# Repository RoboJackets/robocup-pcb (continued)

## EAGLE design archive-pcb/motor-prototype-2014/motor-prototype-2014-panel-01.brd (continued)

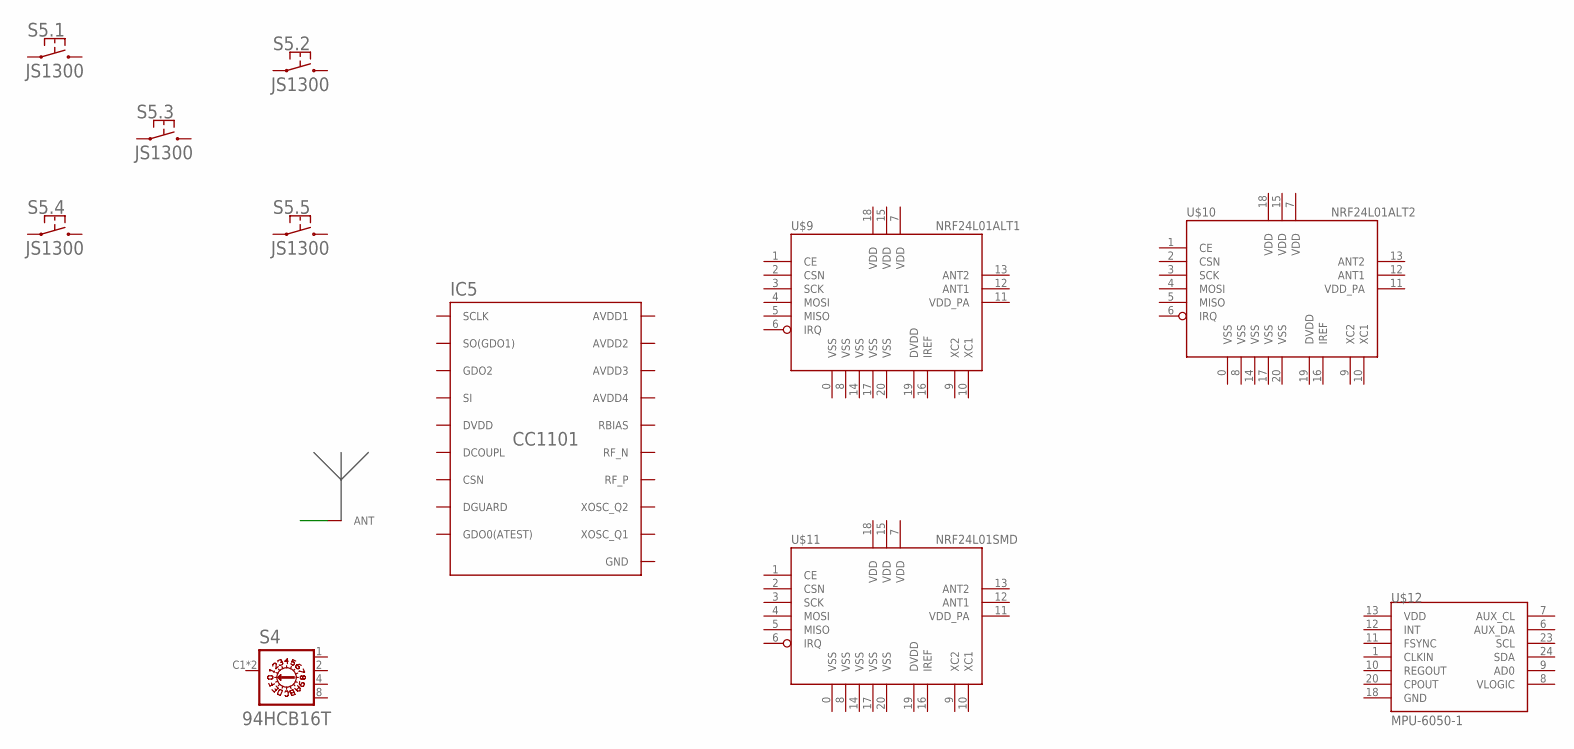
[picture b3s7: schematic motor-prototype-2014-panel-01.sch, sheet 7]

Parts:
916MHZ: ANT-916-CHP-T; ANT-916-CHP
IC5: CC1101; QLP20
S4: 94HCB16T; HEX
S5: JS1300
U$9: NRF24L01ALT1; QFN20_ALT1
U$10: NRF24L01ALT2; QFN20_ALT2
U$11: NRF24L01SMD; QFN20
U$12: MPU-6050-1; QFN-24-4MM2

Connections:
ANT_COPPER: 916MHZ.ANT
DVDD: U$9.19 (DVDD), U$10.19 (DVDD), U$11.19 (DVDD)
VDD: U$9.7 (VDD), U$9.15 (VDD), U$9.18 (VDD), U$10.7 (VDD), U$10.15 (VDD), U$10.18 (VDD), U$11.7 (VDD), U$11.15 (VDD), U$11.18 (VDD); also elsewhere on the board
VDD_PA: U$9.11 (VDD_PA), U$10.11 (VDD_PA), U$11.11 (VDD_PA)
VSS: U$9.0 (VSS), U$9.8 (VSS), U$9.14 (VSS), U$9.17 (VSS), U$9.20 (VSS), U$10.0 (VSS), U$10.8 (VSS), U$10.14 (VSS), U$10.17 (VSS), U$10.20 (VSS), U$11.0 (VSS), U$11.8 (VSS), U$11.14 (VSS), U$11.17 (VSS), U$11.20 (VSS); also elsewhere on the board

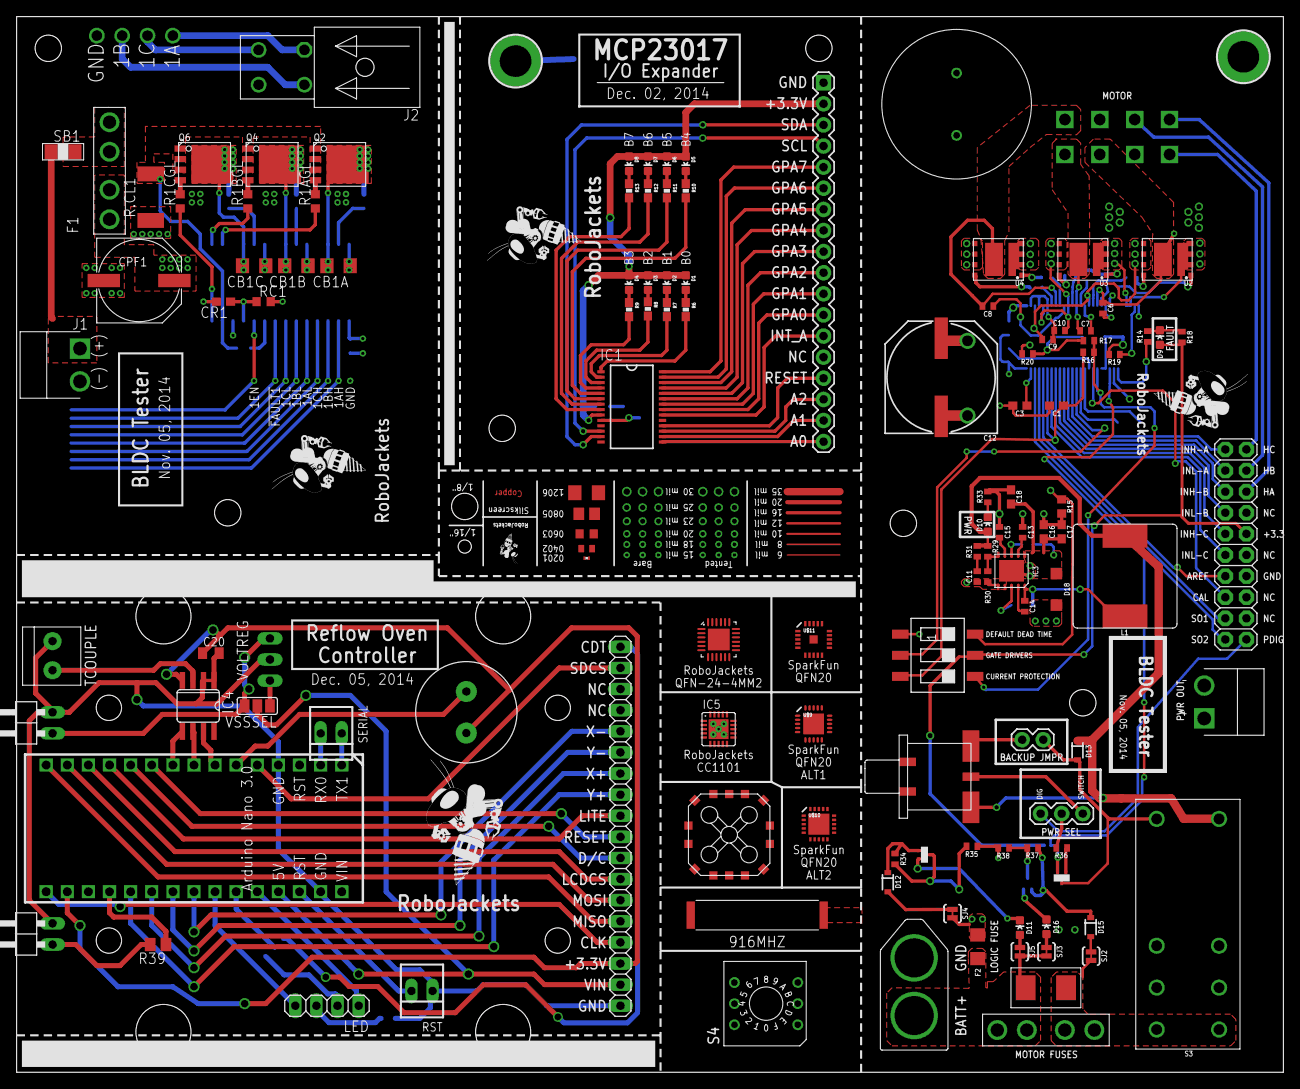
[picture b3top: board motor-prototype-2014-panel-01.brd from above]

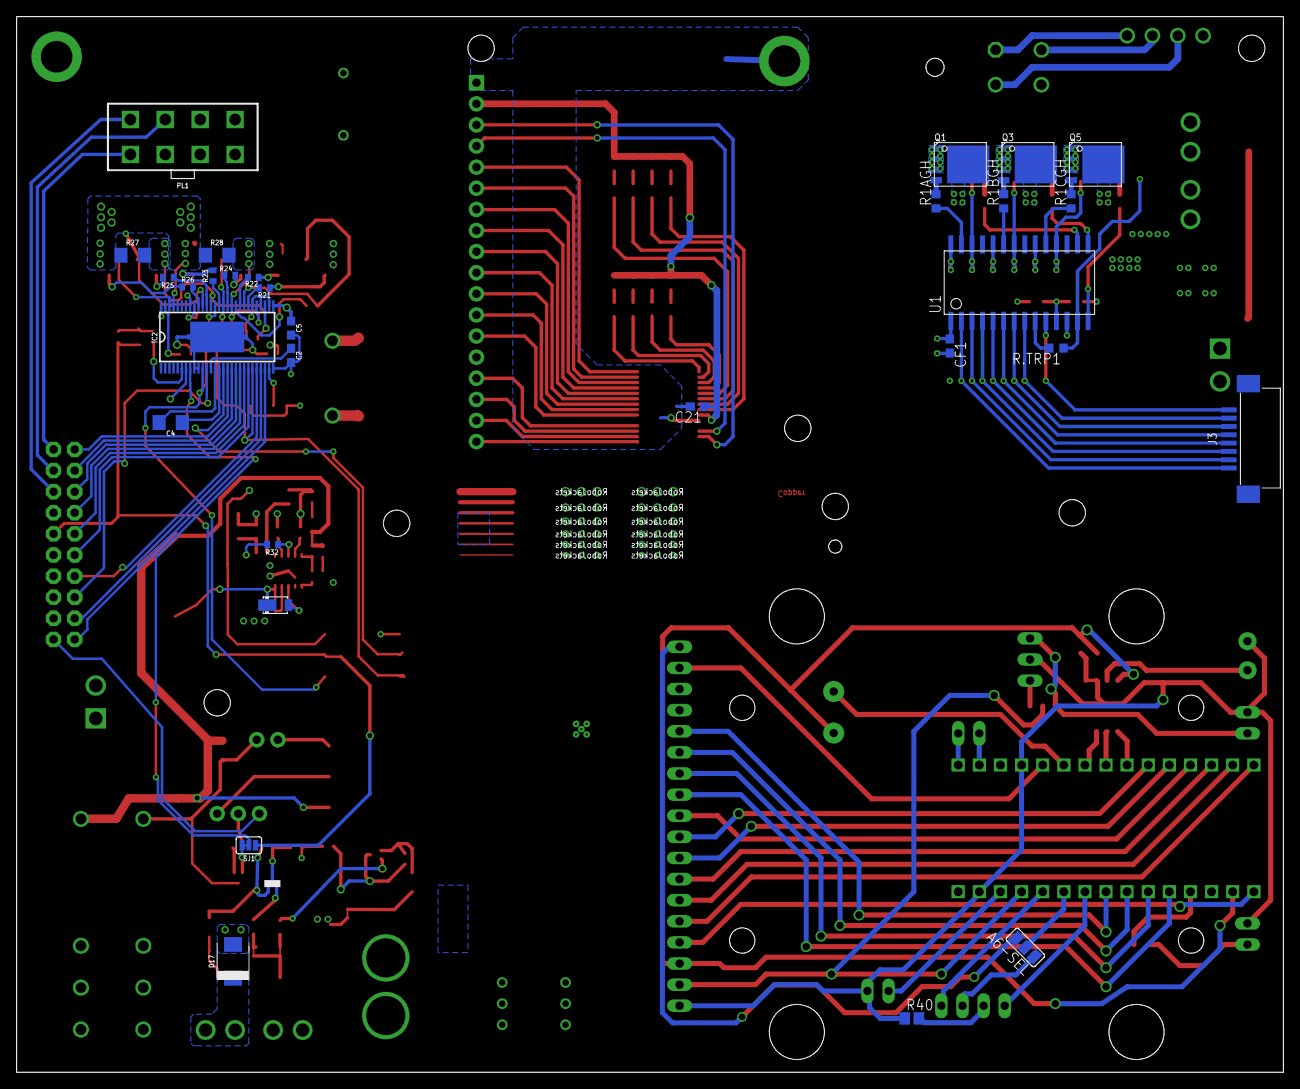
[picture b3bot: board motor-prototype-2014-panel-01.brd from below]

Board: 4 copper layers, 152.4 x 127.0 mm, 162 parts (31 on the bottom side), 172 nets.

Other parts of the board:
U$1, U$5, U$6: ROBOBUZZ_0.6X
U$3: ROBOBUZZ_0.2X
U$8: ROBOBUZZ_0.8X

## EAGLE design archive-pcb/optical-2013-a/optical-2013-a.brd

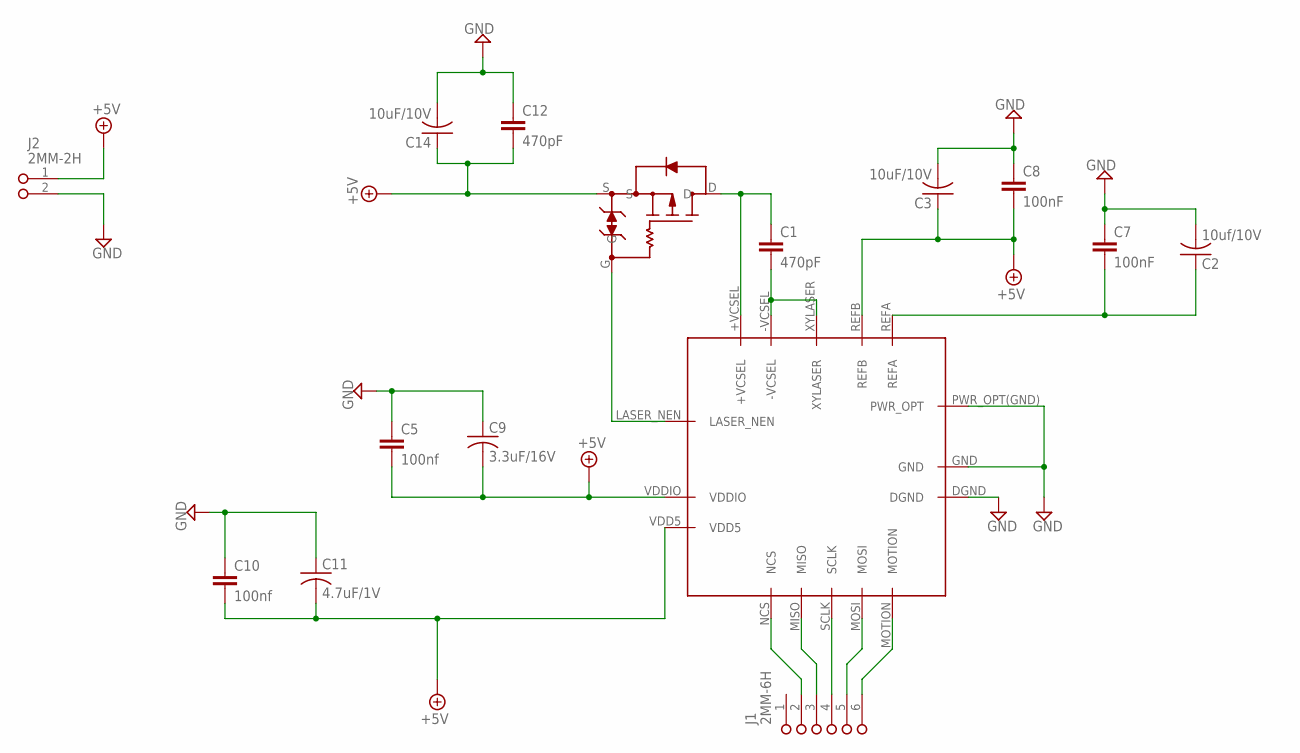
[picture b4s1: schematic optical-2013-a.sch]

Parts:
C1, C12: 470pF; C1005
C2: 10uf/10V; C1005
C3, C14: 10uF/10V; C1005
C5, C10: 100nf; C1005
C7, C8: 100nF; C1005
C9: 3.3uF/16V; C1005
C11: 4.7uF/1V; C1005
J1: 2MM-6H; 2MM-6-H
J2: 2MM-2H; 2MM-2-H
U$1: OPTICAL_SENSOR; ADNS-9500
U$2: P-CHANNEL_MOSFET; NTA4151P

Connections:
+5V: C3.1, C5.2, C8.2, C9.2, C10.2, C11.2, C12.2, C14.1, J2.1, U$1.REFB, U$1.VDD5, U$1.VDDIO, U$2.S
GND: C2.2, C3.2, C5.1, C7.1, C8.1, C9.1, C10.1, C11.1, C12.1, C14.2, J2.2, U$1.DGND, U$1.GND, U$1.PWR_OPT(GND) (PWR_OPT)
unnamed: J1.5, U$1.MOSI
unnamed: J1.6, U$1.MOTION
unnamed: J1.4, U$1.SCLK
unnamed: J1.3, U$1.MISO
unnamed: J1.2, U$1.NCS
unnamed: U$1.LASER_NEN, U$2.G
unnamed: C1.1, U$1.+VCSEL, U$2.D
unnamed: C1.2, U$1.-VCSEL, U$1.XYLASER
unnamed: C2.1, C7.2, U$1.REFA

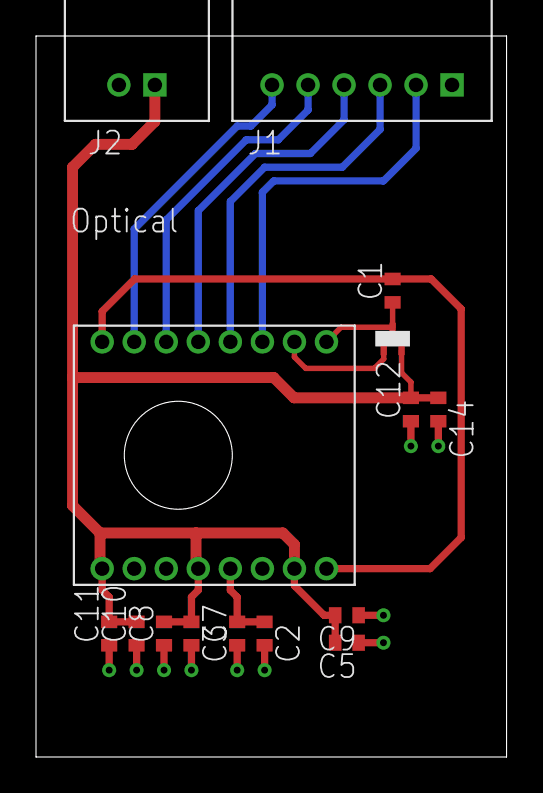
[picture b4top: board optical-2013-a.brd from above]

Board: 2 copper layers, 26.1 x 40.1 mm, 15 parts (0 on the bottom side), 11 nets.

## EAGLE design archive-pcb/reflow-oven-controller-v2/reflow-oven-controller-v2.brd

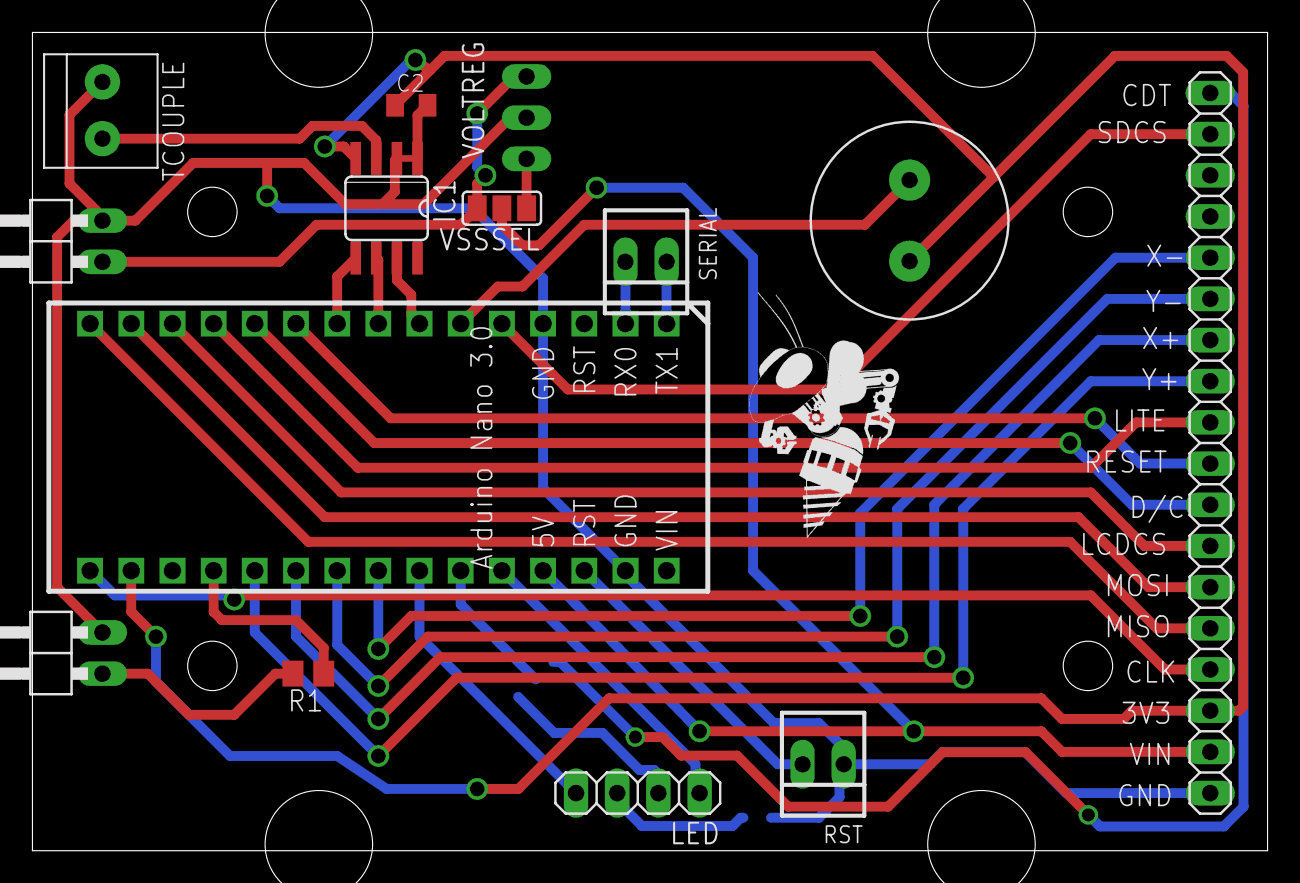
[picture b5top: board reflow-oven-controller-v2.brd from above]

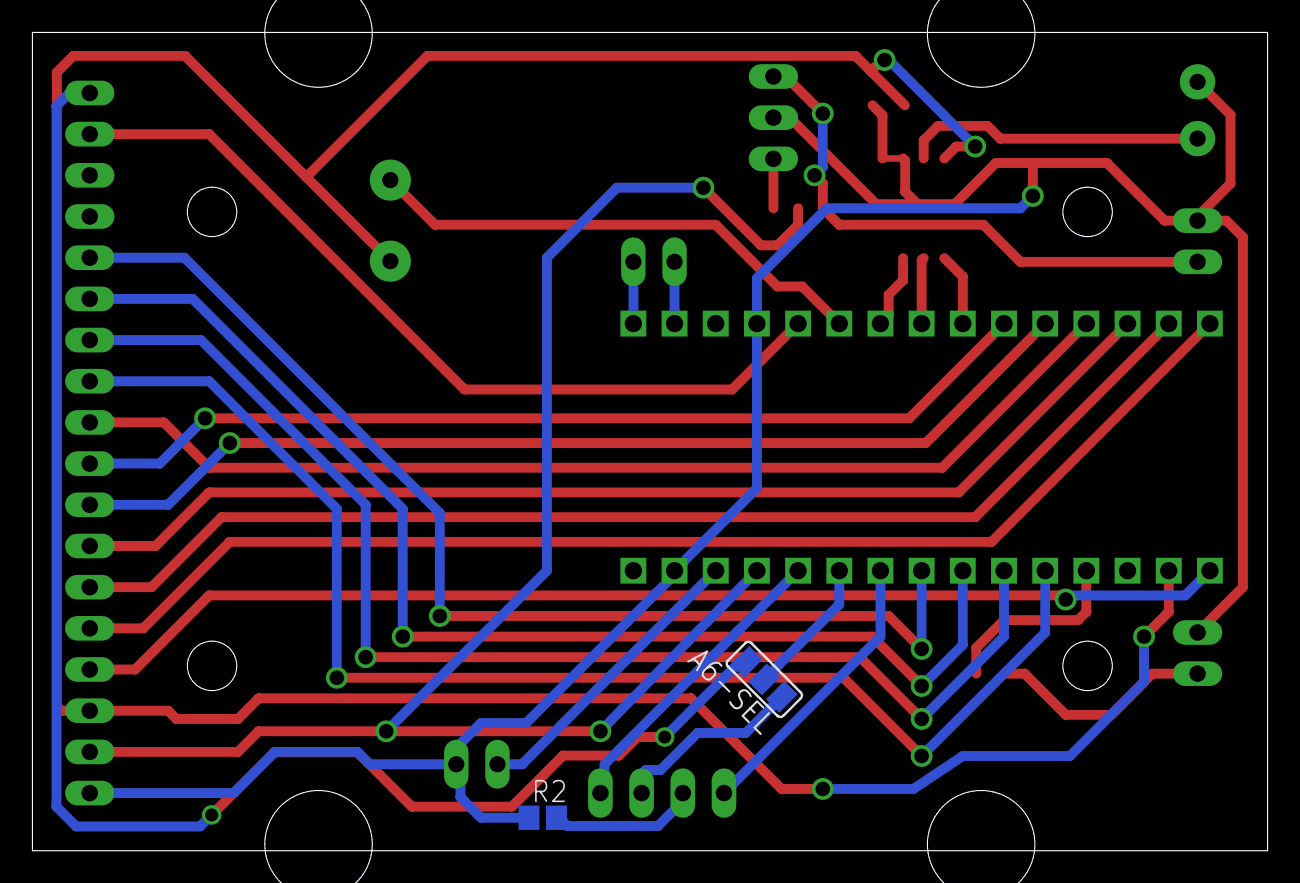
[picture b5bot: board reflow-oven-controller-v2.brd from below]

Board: 2 copper layers, 76.2 x 50.5 mm, 17 parts (2 on the bottom side), 33 nets.

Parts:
A6-SEL: SJ_2
C2: 0.1uF; C0805K
IC1: MAX6675; SO08
JP1: Relay Signal; 1X02/90
JP2: 5VIN; 1X02/90
JP4: 1X18
LED: RGB Led Common Anode; 1X04
R1: 60; M0805
R2: R0805
RST: 22-23-2021
SERIAL: 22-23-2021
SP1: Speaker; PS12
TCOUPLE: 1X2-3.5MM; 3.5MMTERM
U$1: ANANO3.3; ANANO3.0
U$2: ROBOBUZZ_0.8X
VOLTREG: 78SR
VSSSEL: SJ_2

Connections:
A0: R1.1, U$1.A0
A5: LED.4, U$1.A5
A6: A6-SEL.2, U$1.A6
A7: LED.1, U$1.A7
BACKLIGHT: JP4.10, U$1.D9
CARDDET: A6-SEL.3, JP4.18
D/C: JP4.8, U$1.D8
DO: IC1.7, U$1.D4
GND: C2.2, IC1.1, IC1.2, JP1.2, JP2.2, JP4.1, R2.1, RST.1, TCOUPLE.2, U$1.GND, U$1.GND2, VOLTREG.GND
LCDCS: JP4.7, U$1.D10
MISO: JP4.5, U$1.D12
MOSI: JP4.6, U$1.D11
unnamed: IC1.3, TCOUPLE.1
unnamed: A6-SEL.1, LED.2
unnamed: JP1.1, R1.2
unnamed: LED.3, R2.2
REGOUT: VOLTREG.OUT, VSSSEL.1
RESET: JP4.9, U$1.D7
RST2: RST.2, U$1.RST2
RX0: SERIAL.2, U$1.RX0
SCLK: JP4.4, U$1.D13
SDCS: JP4.17, U$1.D2
SPK: SP1.P$1, U$1.D3
TCS: IC1.6, U$1.D5
TRANSIN: JP2.1, VOLTREG.IN, VSSSEL.3
TSCK: IC1.5, U$1.D6
TX1: SERIAL.1, U$1.TX1
VCC: JP4.2, U$1.5V, VSSSEL.2
VSS: C2.1, IC1.4, JP4.3, SP1.P$2, U$1.3V3
X+: JP4.12, U$1.A2
X-: JP4.14, U$1.A4
Y+: JP4.11, U$1.A1
Y-: JP4.13, U$1.A3

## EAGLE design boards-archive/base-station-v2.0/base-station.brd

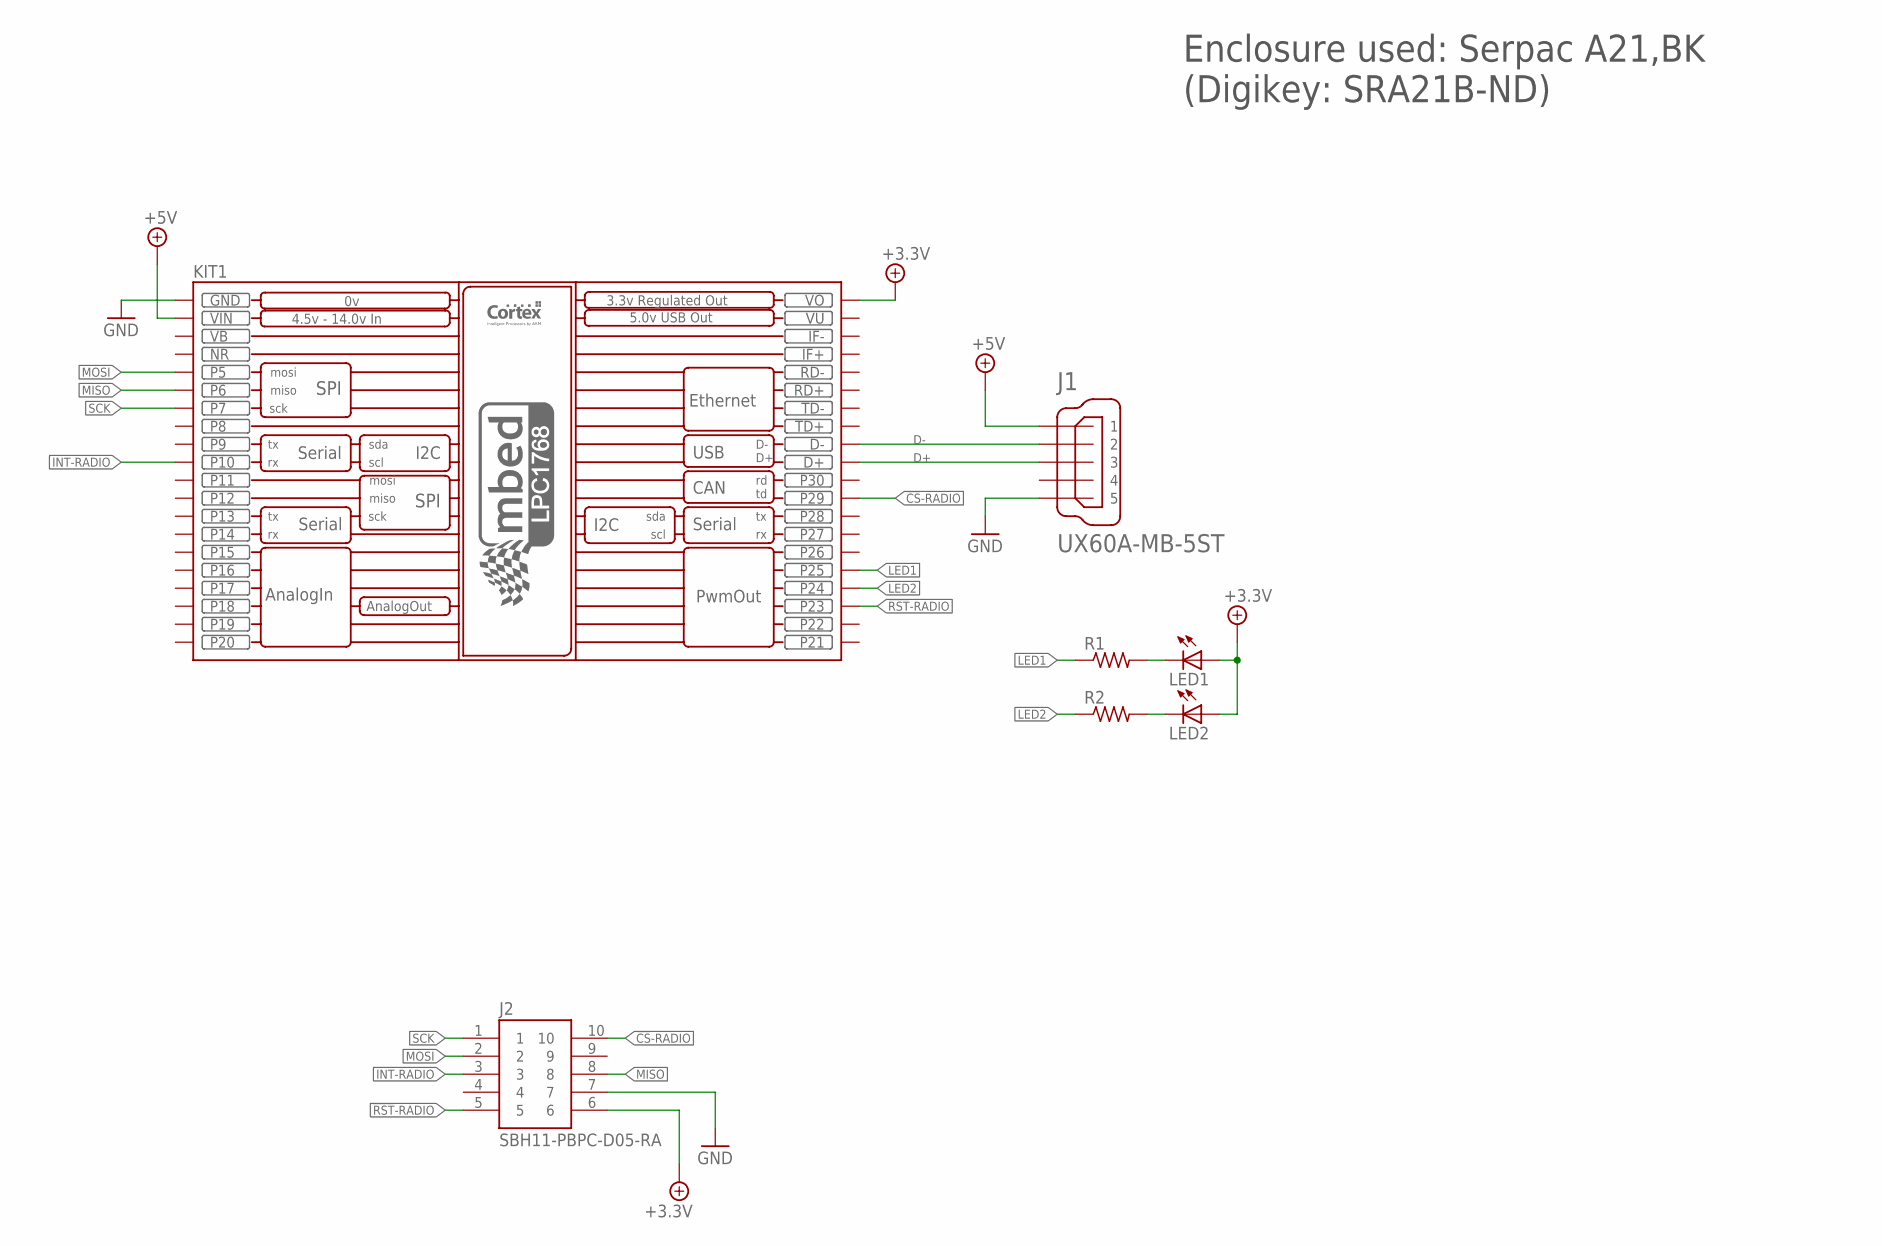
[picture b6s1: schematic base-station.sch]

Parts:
J1: UX60A-MB-5ST
J2: SBH11-PBPC-D05-RA; SBH11-*-D05-RA
KIT1: MBED_NXP_LPC1768; MBED-KIT
LED1, LED2: LED3MM
R1, R2: R-US_R0603; R0603

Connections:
!CS!-RADIO: J2.10, KIT1.P$29 (P29)
!RST!-RADIO: J2.5, KIT1.P$23 (P23)
+3.3V: J2.6, KIT1.VOUT (VO), LED1.A, LED2.A
+5V: J1.1, KIT1.VIN
D+: J1.3, KIT1.D+
D-: J1.2, KIT1.D-
GND: J1.5, J2.7, KIT1.GND
INT-RADIO: J2.3, KIT1.P$10 (P10)
LED1: KIT1.P$25 (P25), R1.1
LED2: KIT1.P$24 (P24), R2.1
MISO: J2.8, KIT1.P$6 (P6)
MOSI: J2.2, KIT1.P$5 (P5)
unnamed: LED1.K (C), R1.2
unnamed: LED2.K (C), R2.2
SCK: J2.1, KIT1.P$7 (P7)
VB: KIT1.VB
VU: KIT1.VU

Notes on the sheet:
Enclosure used: Serpac A21,BK (Digikey: SRA21B-ND)

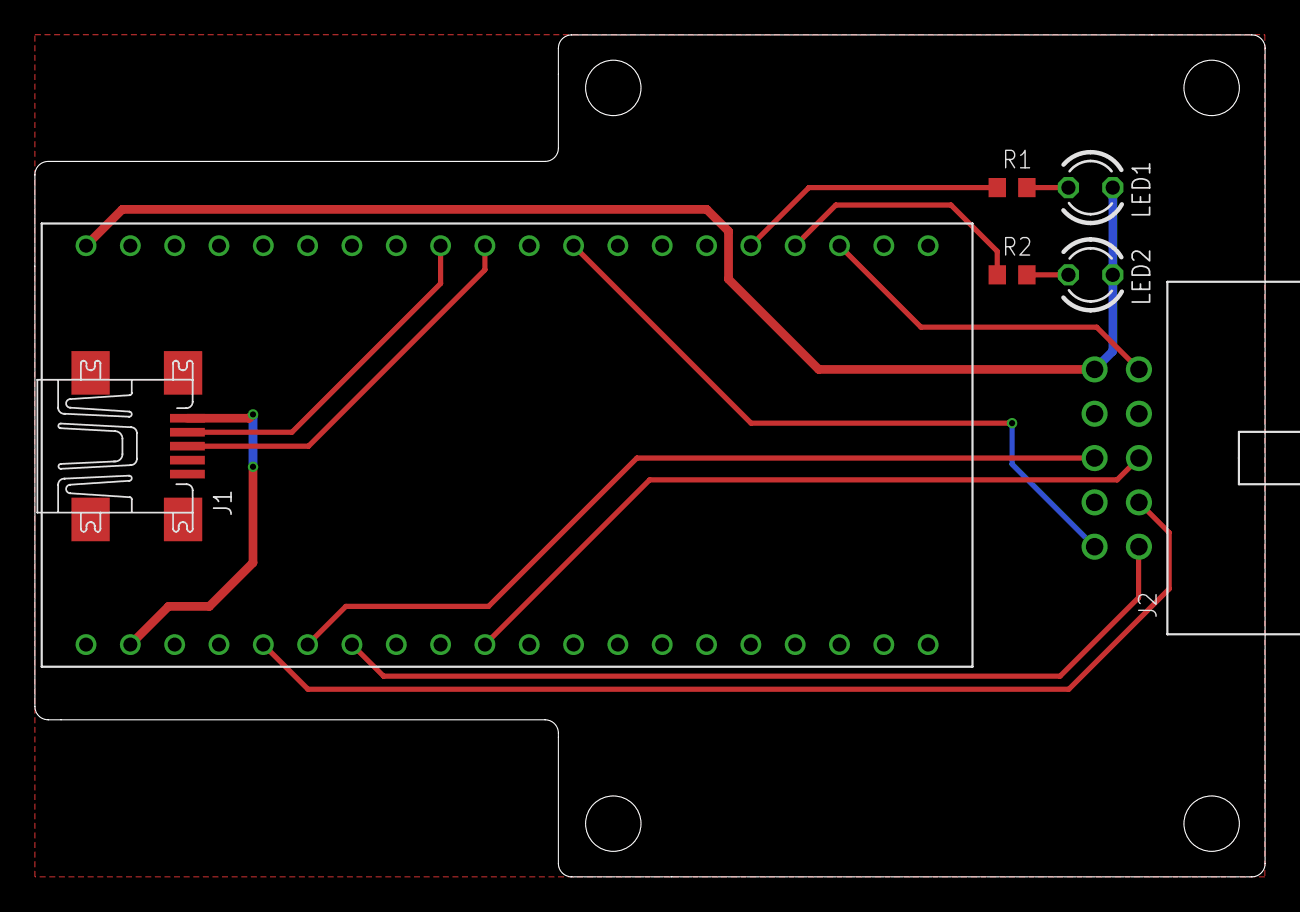
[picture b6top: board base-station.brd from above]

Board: 2 copper layers, 70.5 x 48.2 mm, 7 parts (0 on the bottom side), 15 nets.
